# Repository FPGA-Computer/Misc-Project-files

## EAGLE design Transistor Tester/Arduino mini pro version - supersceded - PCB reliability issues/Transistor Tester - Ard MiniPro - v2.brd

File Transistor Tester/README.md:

Licenses:

Firmware written by me are licensed under GPL v3.

Hardware is licensed under CC BY-4.0
https://creativecommons.org/licenses/by/4.0/

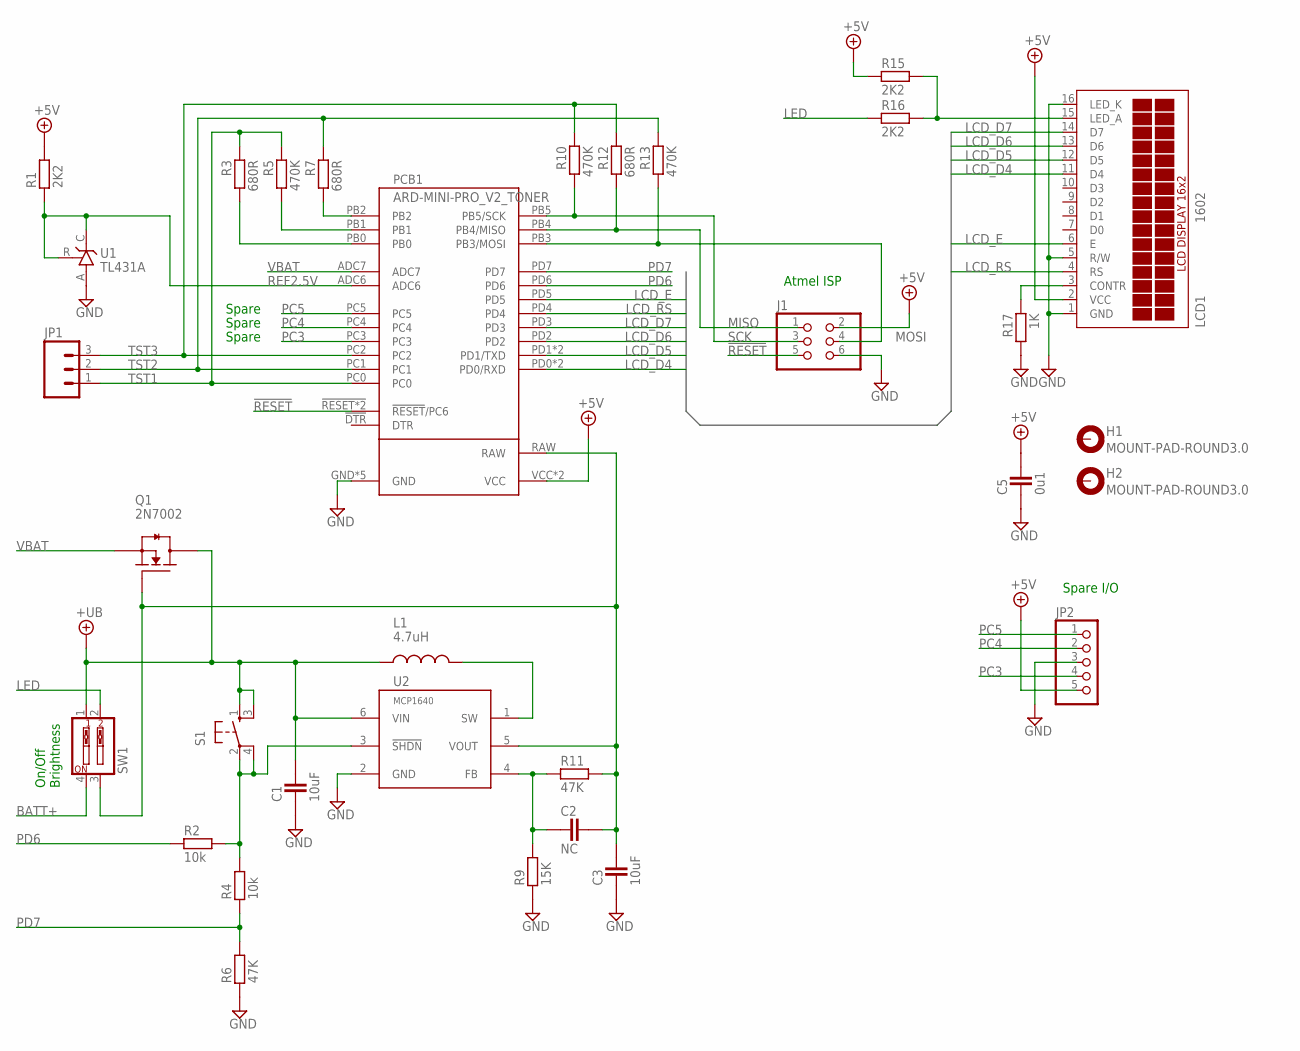
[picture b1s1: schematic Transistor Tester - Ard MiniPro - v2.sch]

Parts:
C1, C3: 10uF; CAPC2012X145AN
C2: NC; CAPC2012X145AN
C5: 0u1; CAPC1608X92N
H1, H2: MOUNT-PAD-ROUND3.0; 3,0-PAD
J1: PINHD-2X3_2.54; 2X03
JP1: M03POLAR; MOLEX-1X3
JP2: PINHD-1X5; 1X05
L1: 4.7uH; CD43
LCD1: 1602; TUXGR_16X2_R2_NM
PCB1: ARD-MINI-PRO_V2_TONER; ARDUINO-PRO-MINI_V2_TONER
Q1: 2N7002; SOT95P280X135-3N
R1, R15, R16: 2K2; RESC1608X55N
R2, R4: 10k; RESC1608X55N
R3, R7, R12: 680R; RESC1608X55N
R5, R10, R13: 470K; RESC1608X55N
R6, R11: 47K; RESC1608X55N
R9: 15K; RESC1608X55N
R17: 1K; RESC1608X55N
S1: MOM_SWTH; MOM_SW
SW1: SW_DIP-2; EDG-02
U1: TL431A; TO92-CLP
U2: MCP1640; SOT26

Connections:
!RESET: J1.5, PCB1.!RESET (!RESET!/PC6), PCB1.!RESET@3 (!RESET!/PC6)
!SHUTDN: R2.2, R4.2, S1.2 (3), S1.4, U2.3 (!SHDN)
+5V: C5.2, J1.2, JP2.5, LCD1.2 (VCC), PCB1.VCC, PCB1.VCC@2 (VCC), R1.2, R15.1
+UB: C1.2, L1.1, Q1.3 (D), S1.1, S1.3 (2), SW1.1, U2.6 (VIN)
BATT+: SW1.4
GND: C1.1, C3.1, C5.1, J1.6, JP2.3, LCD1.1 (GND), LCD1.5 (R/W), LCD1.16 (LED_K), PCB1.GND, PCB1.GND@1 (GND), PCB1.GND@2 (GND), PCB1.GND@3 (GND), PCB1.GND@5 (GND), R6.1, R9.1, R17.2, U1.A, U2.2 (GND)
LCD_A: LCD1.15 (LED_A), R15.2, R16.2
LCD_D4: LCD1.11 (D4), PCB1.PD0 (PD0/RXD), PCB1.PD0@2 (PD0/RXD)
LCD_D5: LCD1.12 (D5), PCB1.PD1 (PD1/TXD), PCB1.PD1@2 (PD1/TXD)
LCD_D6: LCD1.13 (D6), PCB1.PD2
LCD_D7: LCD1.14 (D7), PCB1.PD3
LCD_E: LCD1.6 (E), PCB1.PD5
LCD_RS: LCD1.4 (RS), PCB1.PD4
LED: R16.1, SW1.2
MISO: J1.1, PCB1.PB4 (PB4/MISO), R12.2
MOSI: J1.4, PCB1.PB3 (PB3/MOSI), R13.2
unnamed: L1.2, U2.1 (SW)
unnamed: C2.2, C3.2, PCB1.RAW, Q1.1 (G), R11.2, SW1.3, U2.5 (VOUT)
unnamed: PCB1.PB0, R3.2
unnamed: PCB1.PB1, R5.2
unnamed: PCB1.PB2, R7.2
unnamed: C2.1, R9.2, R11.1, U2.4 (FB)
unnamed: LCD1.3 (CONTR), R17.1
PC3: JP2.4, PCB1.PC3
PC4: JP2.2, PCB1.PC4
PC5: JP2.1, PCB1.PC5
PD6: PCB1.PD6, R2.1
PD7: PCB1.PD7, R4.1, R6.2
REF2.5V: PCB1.ADC6, R1.1, U1.C, U1.R
SCK: J1.3, PCB1.PB5 (PB5/SCK), R10.2
TST1: JP1.1, PCB1.PC0, R3.1, R5.1
TST2: JP1.2, PCB1.PC1, R7.1, R13.1
TST3: JP1.3, PCB1.PC2, R10.1, R12.1
VBAT: PCB1.ADC7, Q1.2 (S)

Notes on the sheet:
Atmel ISP
Spare
Spare I/O
On/Off Brightness

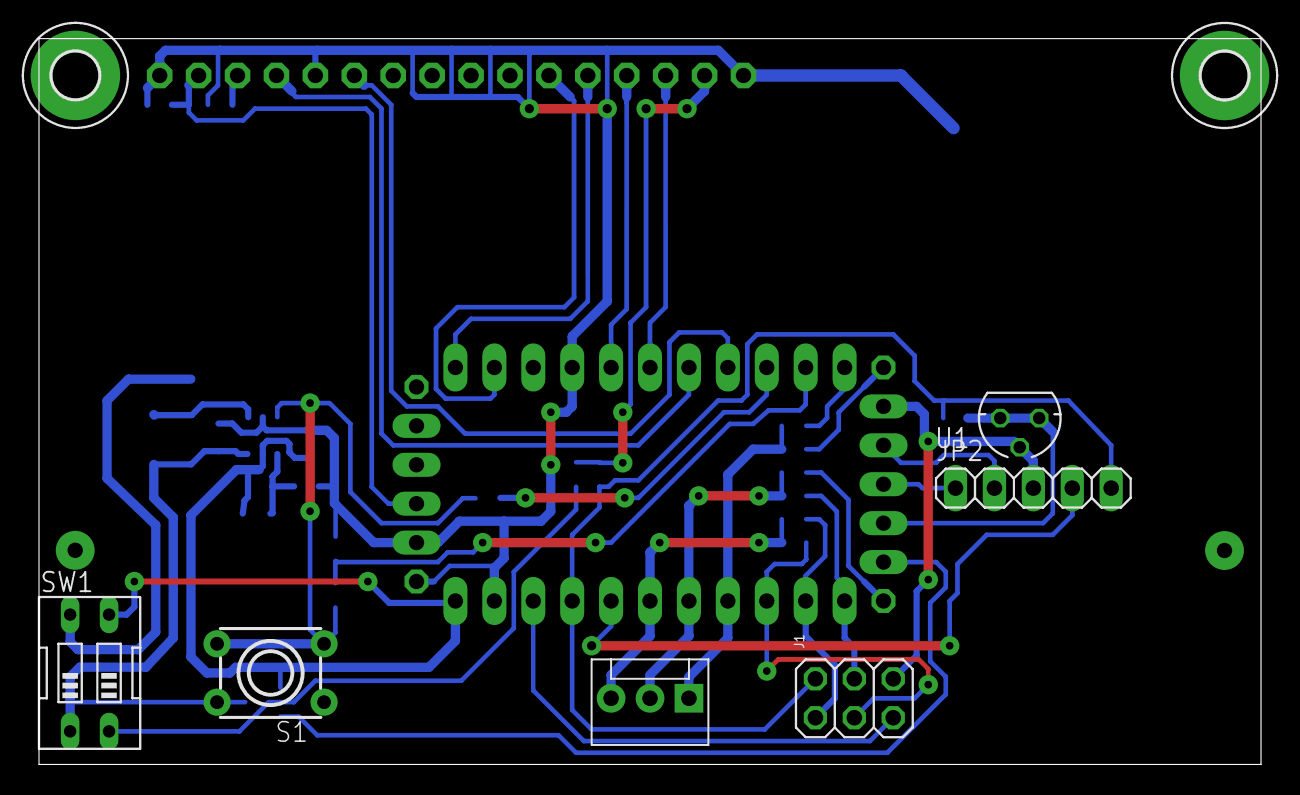
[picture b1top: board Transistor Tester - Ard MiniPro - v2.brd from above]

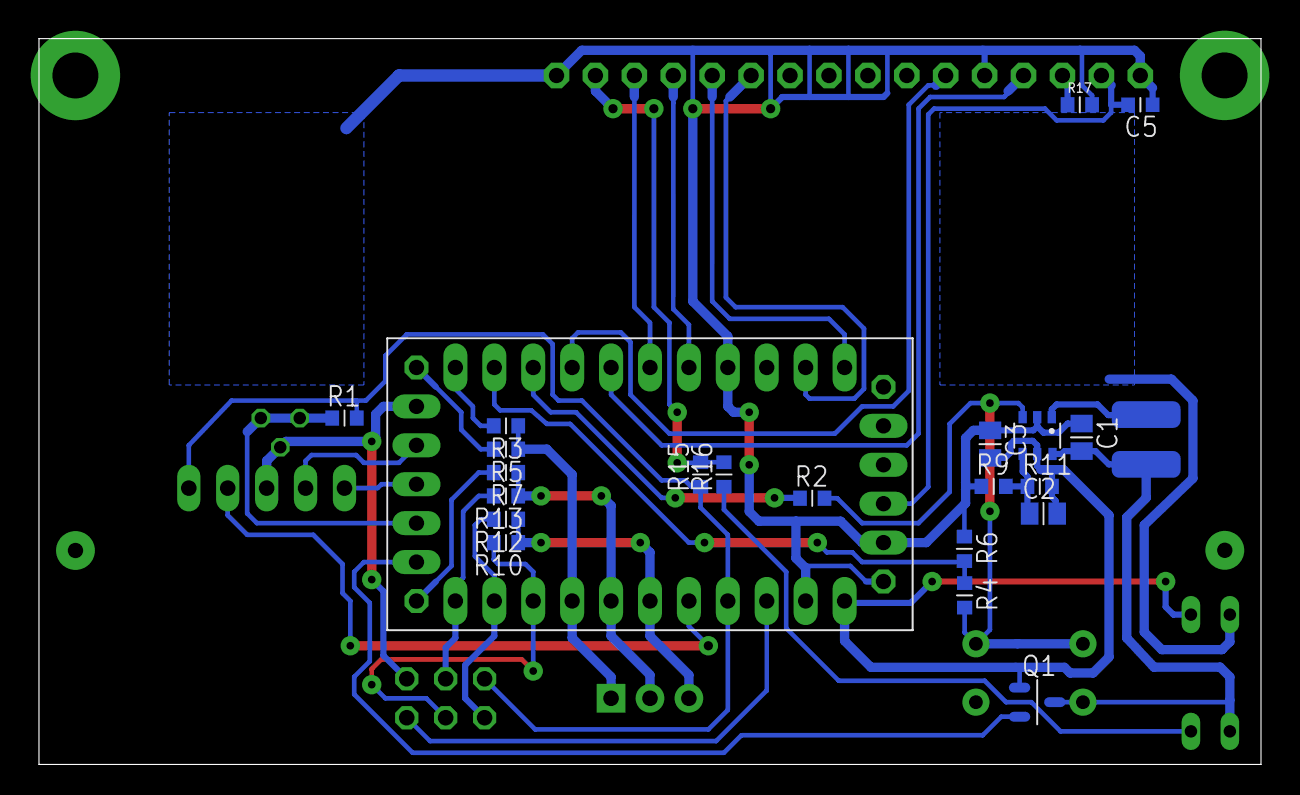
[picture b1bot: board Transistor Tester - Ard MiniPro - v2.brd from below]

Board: 2 copper layers, 79.8 x 47.4 mm, 32 parts (23 on the bottom side), 33 nets.

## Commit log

2018-07-26 Added transistor tester files
2018-07-30 Add DDS project, license
2018-07-30 Added STM8 IRQ header file

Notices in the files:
parts and their libraries:
SparkFun-Connectors: Licensing: Creative Commons ShareAlike 4.0 International - https://creativecommons.org/licenses/by-sa/4.0
